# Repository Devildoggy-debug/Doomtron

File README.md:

# Doomtron
A small Gameboy esque console made to play one of the greatest games ever DOOM 1993, ft a Rasperrby Pi Pico and  TFT Screen.
## <ins>Why Doom1993? (Read the TLDR if you don't want to hear me gush about doom)</ins>
DOOM 1993 is a notorious game made on the Doom engine, heralded as the first 3D game ever. The gem made by id software works by replicating 3D graphics by using several layered 2D sprites giving a 3D feel to it.In honesty it can be called a 2.5D game, the entire game is a 2D optical illusion that looks 3D!!! A wonderful piece of tech and a game that holds up pretty well now too, as the first ever FPS (EXCLUDING WOLFESNSTEIN 3D,which came first but wasn't as popular,also made by id software).Now the main wonder and awesomeness of DOOM 1993 is that it can played on anything, globally among most tech users the questions to test a device are "Can it run Crysis?" among PC users (since it was one of the most graphically and high requirement game at the time) and "Can it run DOOM?" among general device users. It can run on almost anything,and I do mean anything, although it needs to be coded in at times. It can run on,For example:Your phone,most Ti calculators,Your grandma's phone,A potato pc,a Potato (like the vegetable),An Xray machine, A heart rate monitor,etc. And to celebrate such a wonderful game,I decided to make a console tailor made for DOOM 1993,since it can run alongside anything, Why not run solo for once?
<br>
<br>
TLDR; DOOM 1993 can run on most devices, so why not make an exclusive device to run it for once.
## <ins>THE FEATURES<ins>
- Doom 1993 fully playable
- full working button system, including movement ,shooting,runnning,etc.
- usb port for power
<br>
<br>
## <ins>THE PCB<ins>
<br>

<br>
<br>

<br>
<br>

<br>
<br>

<br>
<br>
VERY IMPORTANT:THE FRIMWARE FILES STILL NEED TWEAKING,WHICH I CAN ONLY DO WHEN I PHYSICALLY HAVE THE SCREEN AND PICO SINCE I NEED TO MAKE SEVERAL ADJUSTMENTS AND LIVE TESTS TO MAKE IT WORK PROPERLY ON THE ACTUALPCB

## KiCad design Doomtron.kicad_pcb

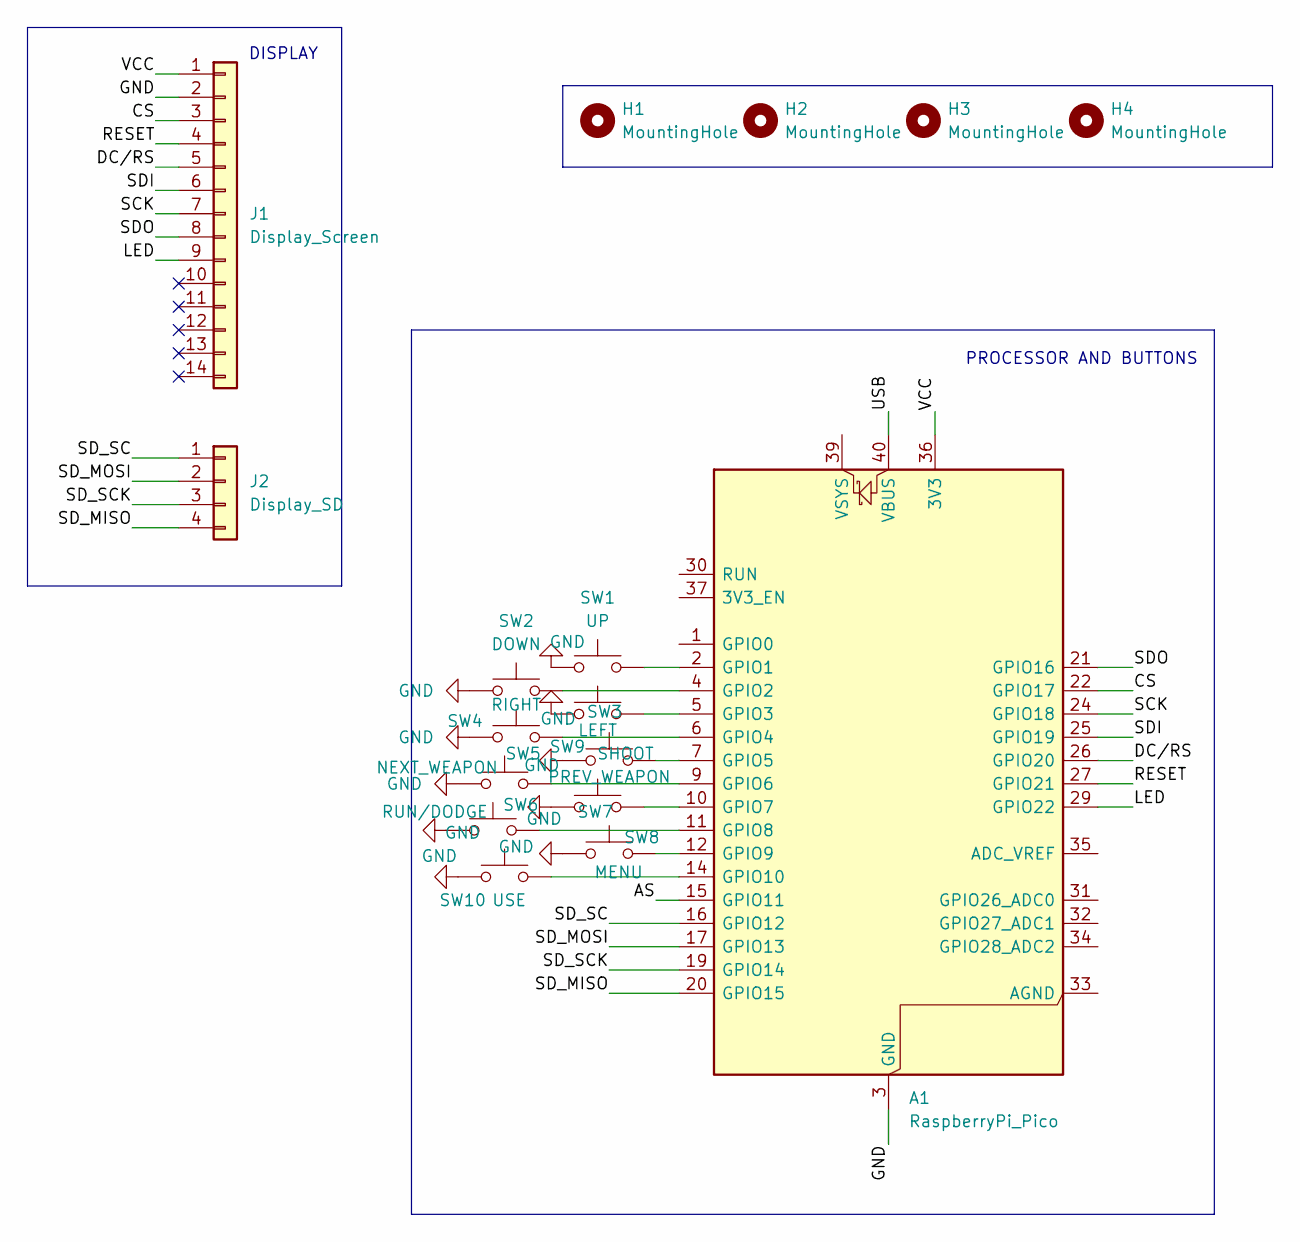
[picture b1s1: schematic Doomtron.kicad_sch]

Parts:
A1: RaspberryPi_Pico; RaspberryPi_Pico_Common_THT
H1, H2, H3, H4: MountingHole; MountingHole_3.2mm_M3
J1: Display_Screen; PinHeader_1x14_P2.54mm_Vertical
J2: Display_SD; PinHeader_1x04_P2.54mm_Vertical
SW1: UP; SW_PUSH_6mm_H5mm
SW2: DOWN; SW_PUSH_6mm_H5mm
SW3: LEFT; SW_PUSH_6mm_H5mm
SW4: RIGHT; SW_PUSH_6mm_H5mm
SW5: NEXT_WEAPON; SW_PUSH_6mm_H5mm
SW6: RUN/DODGE; SW_PUSH_6mm_H5mm
SW7: PREV_WEAPON; SW_PUSH_6mm_H5mm
SW8: MENU; SW_PUSH_6mm_H5mm
SW9: SHOOT; SW_PUSH_6mm_H5mm
SW10: USE; SW_PUSH_6mm_H5mm

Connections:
/AS: A1.15 (GPIO11)
/CS: A1.22 (GPIO17), J1.3
/DC/RS: A1.26 (GPIO20), J1.5
/LED: A1.29 (GPIO22), J1.9
/RESET: A1.27 (GPIO21), J1.4
/SCK: A1.24 (GPIO18), J1.7
/SDI: A1.25 (GPIO19), J1.6
/SDO: A1.21 (GPIO16), J1.8
/SD_MISO: A1.20 (GPIO15), J2.4
/SD_MOSI: A1.17 (GPIO13), J2.2
/SD_SC: A1.16 (GPIO12), J2.1
/SD_SCK: A1.19 (GPIO14), J2.3
/USB: A1.40 (VBUS)
/VCC: A1.36 (3V3), J1.1
GND: A1.3 (GND), A1.8 (GND), A1.13 (GND), A1.18 (GND), A1.23 (GND), A1.28 (GND), A1.38 (GND), J1.2, SW1.1, SW2.1, SW3.1, SW4.1, SW5.1, SW6.1, SW7.1, SW8.1, SW9.1, SW10.1
unnamed: A1.2 (GPIO1), SW1.2
unnamed: A1.4 (GPIO2), SW2.2
unnamed: A1.5 (GPIO3), SW3.2
unnamed: A1.6 (GPIO4), SW4.2
unnamed: A1.7 (GPIO5), SW9.2
unnamed: A1.9 (GPIO6), SW5.2
unnamed: A1.10 (GPIO7), SW7.2
unnamed: A1.11 (GPIO8), SW6.2
unnamed: A1.12 (GPIO9), SW8.2
unnamed: A1.14 (GPIO10), SW10.2

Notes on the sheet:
DISPLAY
PROCESSOR AND BUTTONS

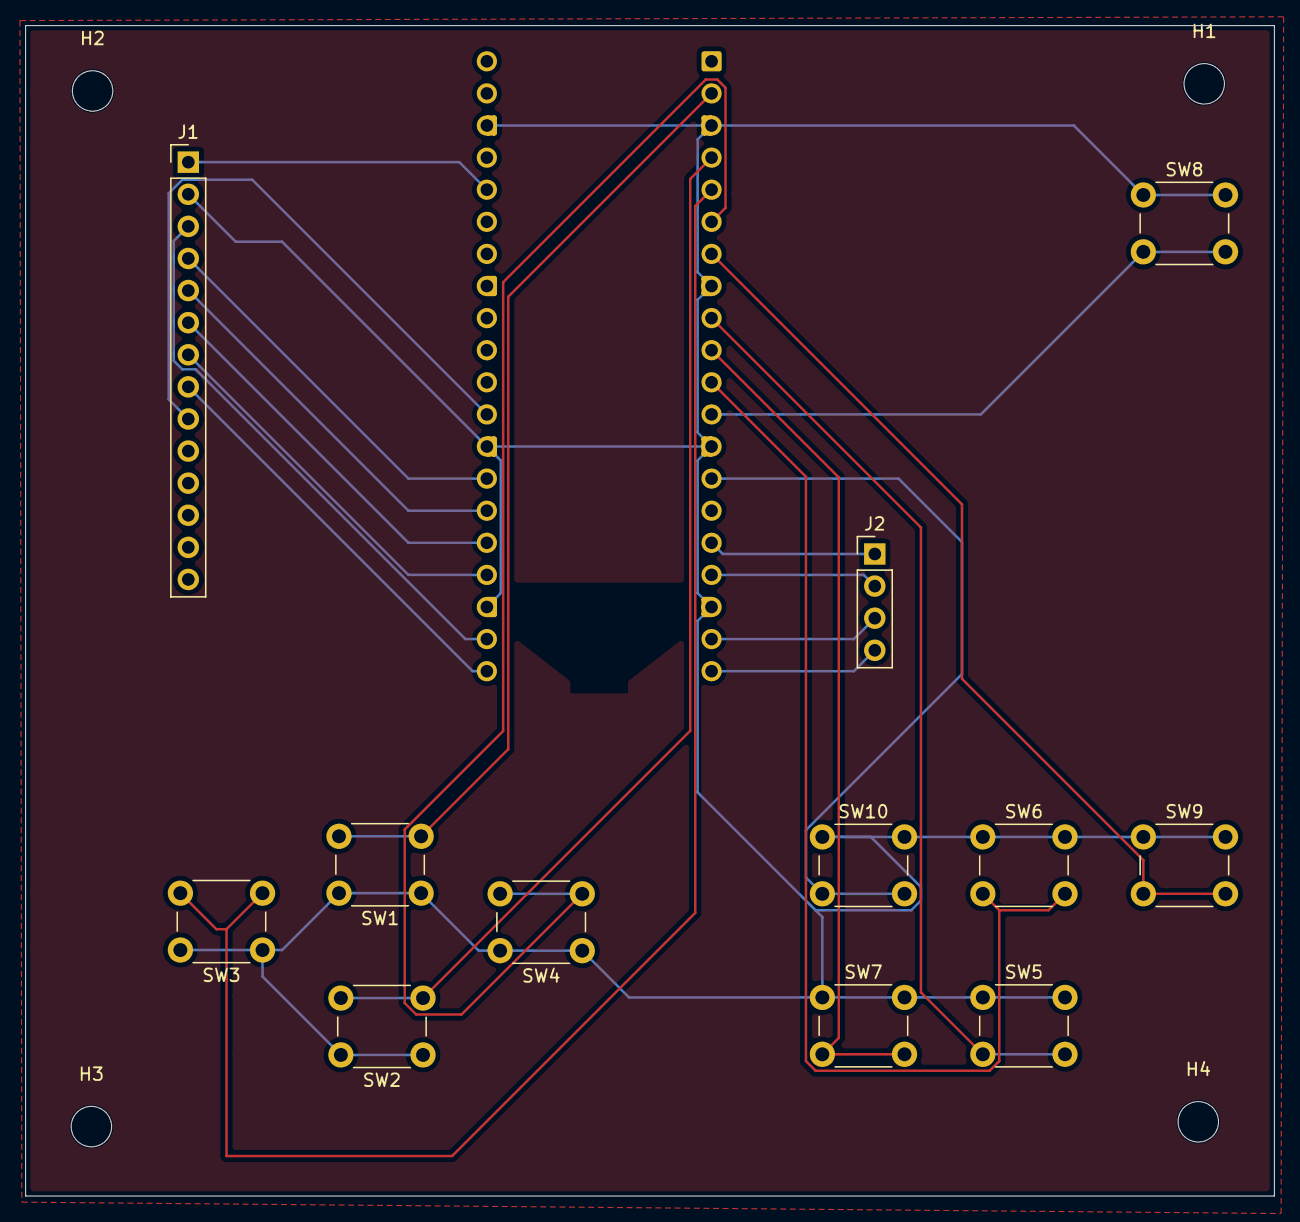
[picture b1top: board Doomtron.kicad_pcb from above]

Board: 2 copper layers, 98.8 x 92.6 mm, 17 parts (1 on the bottom side), 23 nets.
